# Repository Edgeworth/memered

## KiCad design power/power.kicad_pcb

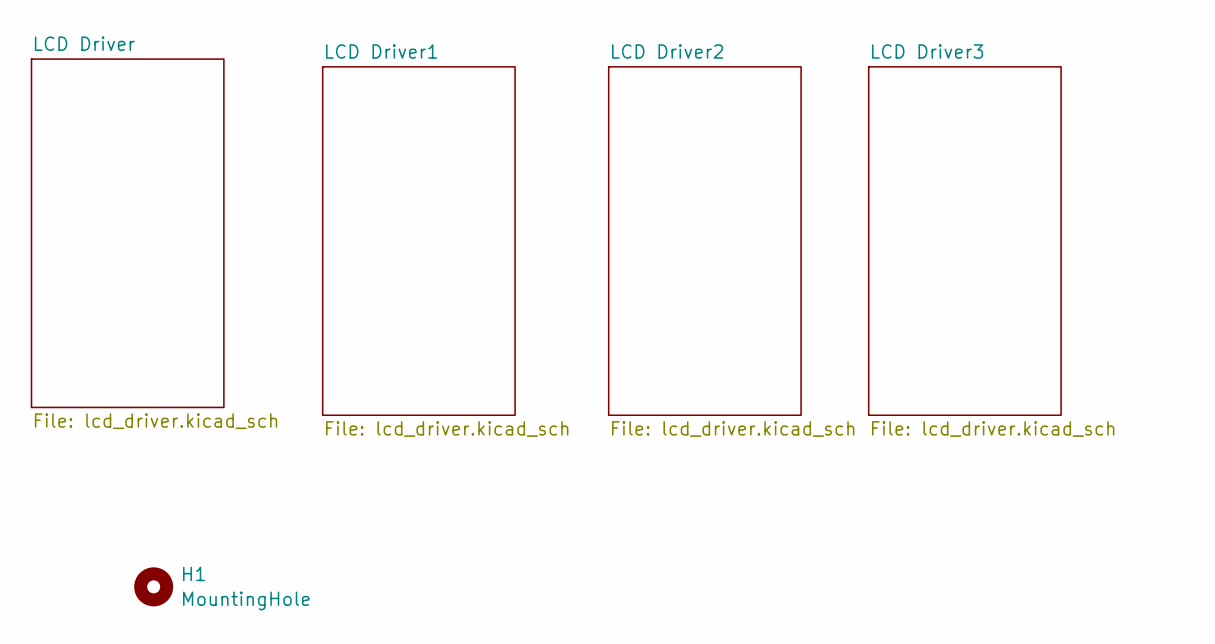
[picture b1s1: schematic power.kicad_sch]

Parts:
H1: MountingHole; MountingHole_2.2mm_M2

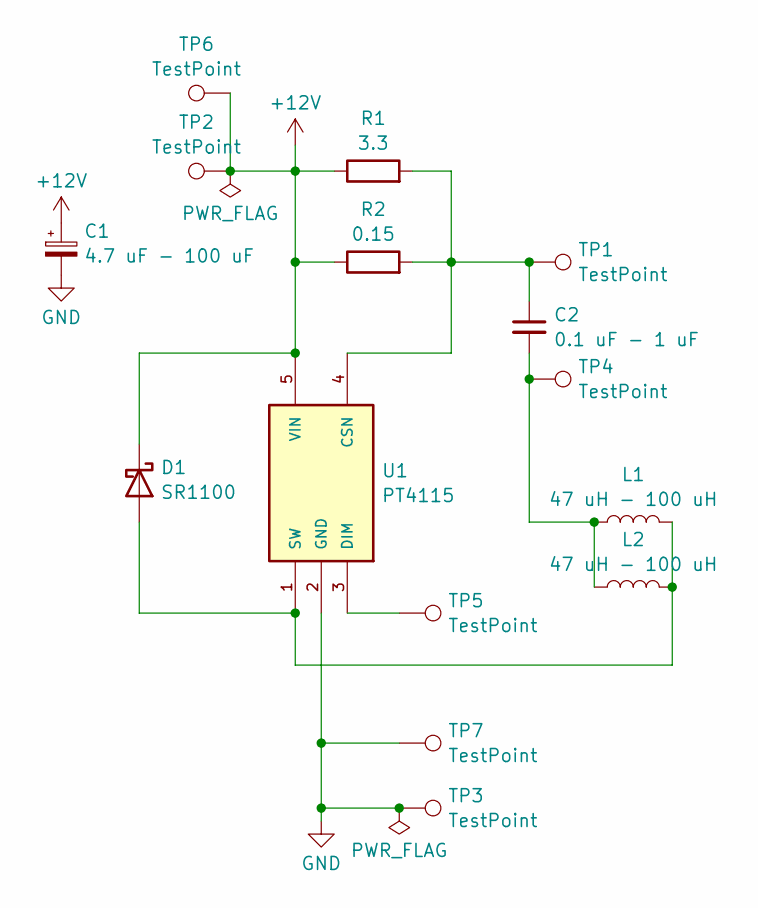
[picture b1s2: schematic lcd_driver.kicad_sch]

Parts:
C1: 4.7 uF - 100 uF; CP_Radial_D6.3mm_P2.50mm
C2: 0.1 uF - 1 uF; C_Disc_D6.0mm_W2.5mm_P5.00mm
D1: SR1100; D_DO-35_SOD27_P7.62mm_Horizontal
L1, L2: 47 uH - 100 uH; L_Axial_L9.5mm_D4.0mm_P12.70mm_Horizontal_Fastron_SMCC
R1: 3.3; R_Axial_DIN0207_L6.3mm_D2.5mm_P7.62mm_Horizontal
R2: 0.15; R_Axial_DIN0207_L6.3mm_D2.5mm_P7.62mm_Horizontal
TP1, TP2, TP3, TP4, TP5: TestPoint; TestPoint_THTPad_D1.5mm_Drill0.7mm
TP6, TP7: TestPoint; TestPoint_THTPad_D3.0mm_Drill1.5mm
U1: PT4115; SOT-89-5

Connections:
+12V: C1.1, D1.1 (K), R1.1, R2.1, TP2.1, TP6.1, U1.5 (VIN); also elsewhere on the board
GND: C1.2, TP3.1, TP7.1, U1.2 (GND); also elsewhere on the board
unnamed: C2.2, L1.1, L2.1, TP4.1
unnamed: D1.2 (A), L1.2, L2.2, U1.1 (SW)
unnamed: C2.1, R1.2, R2.2, TP1.1, U1.4 (CSN)
unnamed: TP5.1, U1.3 (DIM)

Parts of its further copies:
C3, C5, C7: 4.7 uF - 100 uF; CP_Radial_D6.3mm_P2.50mm
C4, C6, C8: 0.1 uF - 1 uF; C_Disc_D6.0mm_W2.5mm_P5.00mm
D2, D3, D4: SR1100; D_DO-35_SOD27_P7.62mm_Horizontal
L3, L4, L5, L6, L7, L8: 47 uH - 100 uH; L_Axial_L9.5mm_D4.0mm_P12.70mm_Horizontal_Fastron_SMCC
R3, R5, R7: 3.3; R_Axial_DIN0207_L6.3mm_D2.5mm_P7.62mm_Horizontal
R4, R6, R8: 0.15; R_Axial_DIN0207_L6.3mm_D2.5mm_P7.62mm_Horizontal
TP8, TP11, TP15, TP18, TP22, TP25: TestPoint; TestPoint_THTPad_D3.0mm_Drill1.5mm
TP9, TP10, TP12, TP13, TP14, TP16, TP17, TP19, TP20, TP21, TP23, TP24, TP26, TP27, TP28: TestPoint; TestPoint_THTPad_D1.5mm_Drill0.7mm
U2, U3, U4: PT4115; SOT-89-5

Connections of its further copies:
+12V: C3.1, C5.1, C7.1, D2.1 (K), D3.1 (K), D4.1 (K), R3.1, R4.1, R5.1, R6.1, R7.1, R8.1, TP8.1, TP9.1, TP15.1, TP16.1, TP22.1, TP23.1, U2.5 (VIN), U3.5 (VIN), U4.5 (VIN); also elsewhere on the board
GND: C3.2, C5.2, C7.2, TP11.1, TP12.1, TP18.1, TP19.1, TP25.1, TP26.1, U2.2 (GND), U3.2 (GND), U4.2 (GND); also elsewhere on the board
unnamed: C4.2, L3.1, L4.1, TP14.1
unnamed: C6.2, L5.1, L6.1, TP21.1
unnamed: C8.2, L7.1, L8.1, TP28.1
unnamed: D2.2 (A), L3.2, L4.2, U2.1 (SW)
unnamed: D3.2 (A), L5.2, L6.2, U3.1 (SW)
unnamed: D4.2 (A), L7.2, L8.2, U4.1 (SW)
unnamed: C4.1, R3.2, R4.2, TP13.1, U2.4 (CSN)
unnamed: TP10.1, U2.3 (DIM)
unnamed: C6.1, R5.2, R6.2, TP20.1, U3.4 (CSN)
unnamed: TP17.1, U3.3 (DIM)
unnamed: C8.1, R7.2, R8.2, TP27.1, U4.4 (CSN)
unnamed: TP24.1, U4.3 (DIM)

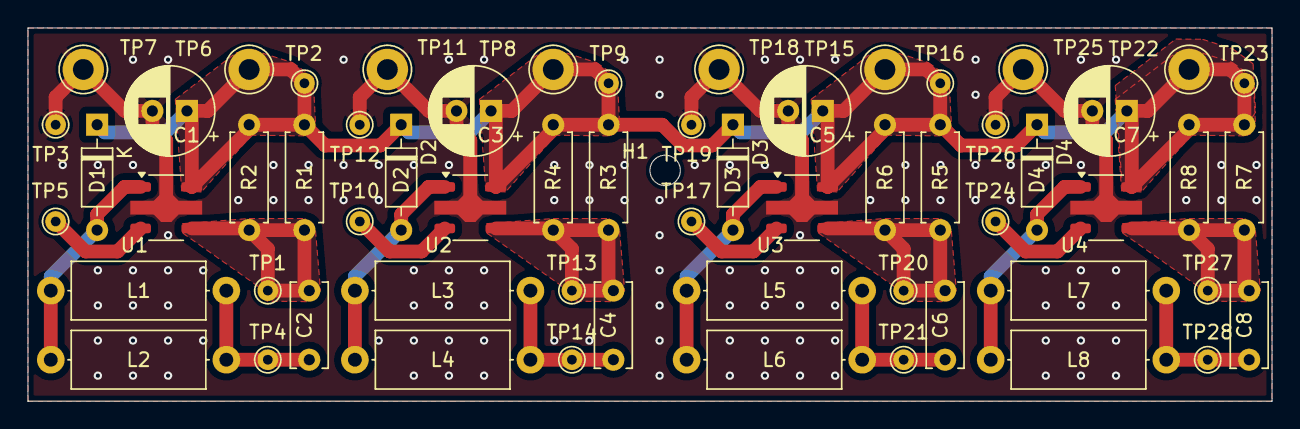
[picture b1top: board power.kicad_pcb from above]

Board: 2 copper layers, 90.0 x 27.0 mm, 61 parts (0 on the bottom side), 18 nets.

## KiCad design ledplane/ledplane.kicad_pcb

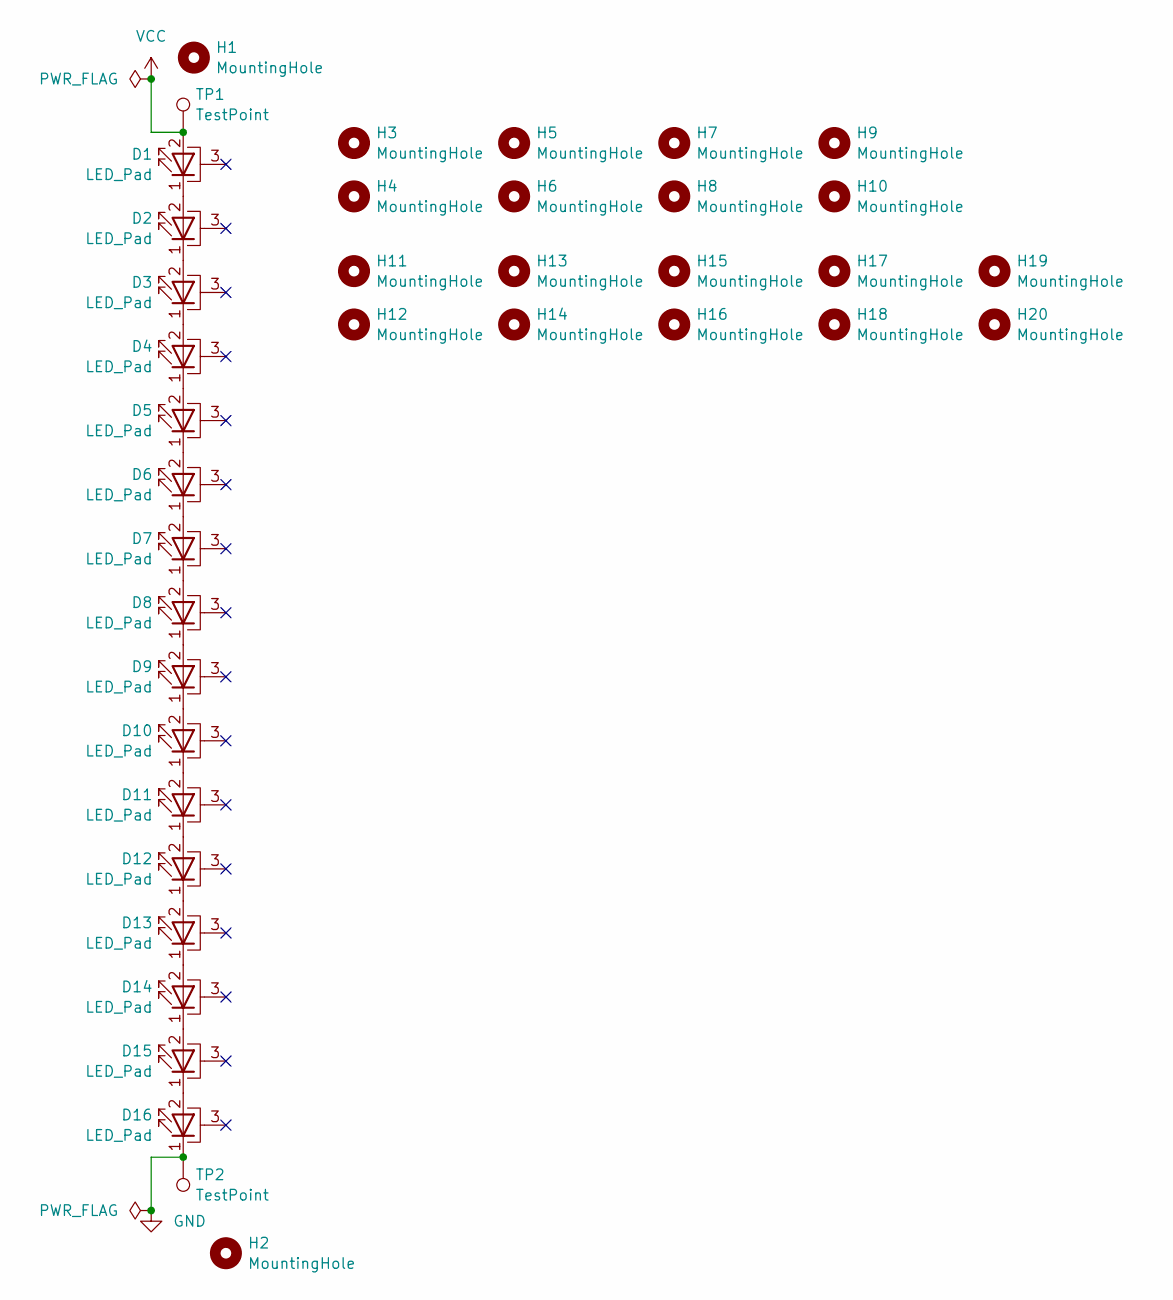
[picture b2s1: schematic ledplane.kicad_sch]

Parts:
D1, D2, D3, D4, D5, D6, D7, D8, D9, D10, D11, D12, D13, D14, D15, D16: LED_Pad; LED_3W_OTDIODE_COMBINED
H1, H2: MountingHole; MountingHole_2.2mm_M2
H3, H4, H5, H6, H7, H8, H9, H10, H11, H12, H13, H14, H15, H16, H17, H18, H19, H20: MountingHole; MountingHole_3.2mm_M3
TP1, TP2: TestPoint; SolderWirePad_1x01_SMD_4x6mm

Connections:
GND: D16.1 (K), TP2.1
unnamed: D1.1 (K), D2.2 (A)
unnamed: D2.1 (K), D3.2 (A)
unnamed: D3.1 (K), D4.2 (A)
unnamed: D4.1 (K), D5.2 (A)
unnamed: D5.1 (K), D6.2 (A)
unnamed: D6.1 (K), D7.2 (A)
unnamed: D7.1 (K), D8.2 (A)
unnamed: D8.1 (K), D9.2 (A)
unnamed: D9.1 (K), D10.2 (A)
unnamed: D10.1 (K), D11.2 (A)
unnamed: D11.1 (K), D12.2 (A)
unnamed: D12.1 (K), D13.2 (A)
unnamed: D13.1 (K), D14.2 (A)
unnamed: D14.1 (K), D15.2 (A)
unnamed: D15.1 (K), D16.2 (A)
VCC: D1.2 (A), TP1.1

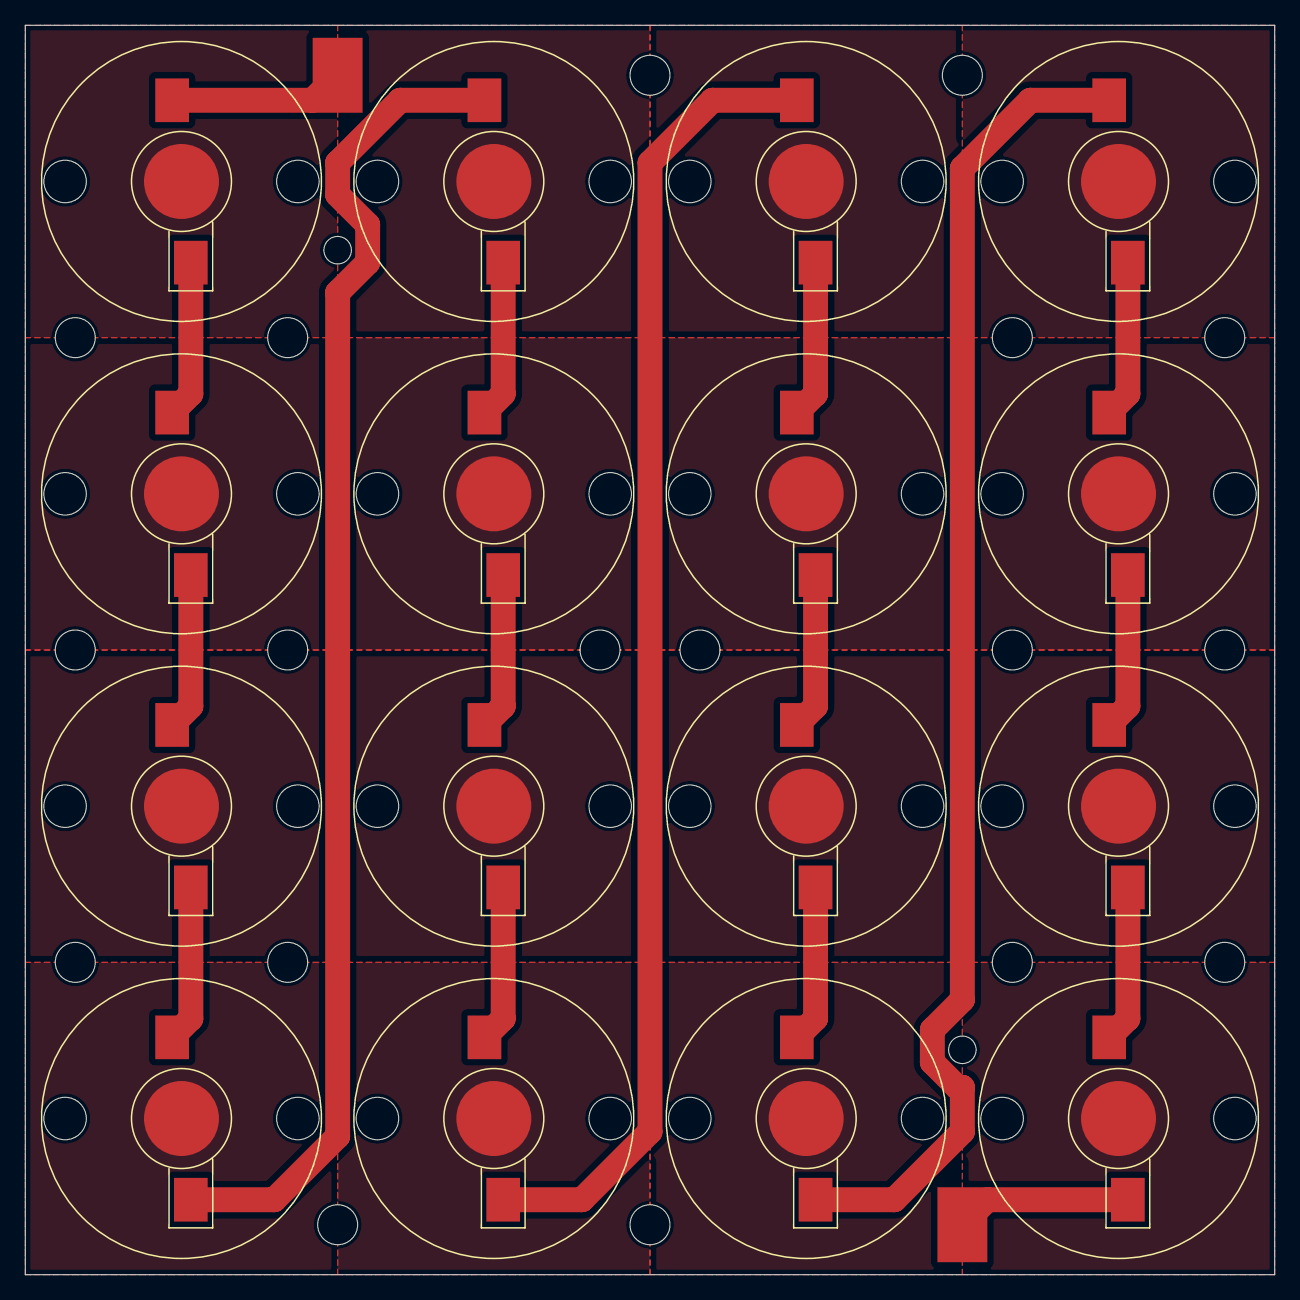
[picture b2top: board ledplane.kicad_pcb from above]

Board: 2 copper layers, 100.0 x 100.0 mm, 38 parts (0 on the bottom side), 17 nets.

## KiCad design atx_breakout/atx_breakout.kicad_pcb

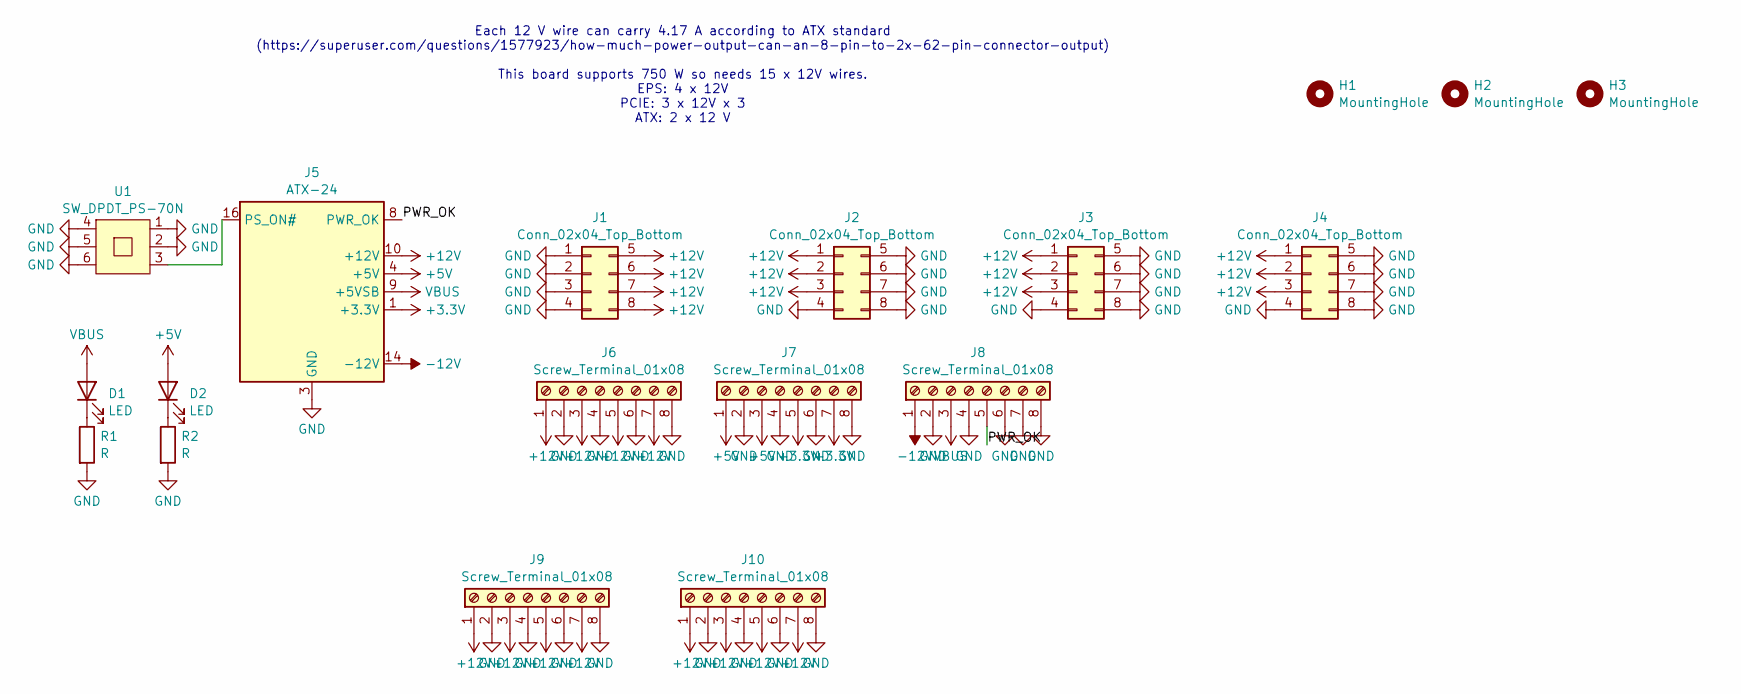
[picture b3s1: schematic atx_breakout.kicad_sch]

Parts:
D1, D2: LED; LED_D5.0mm
H1, H2, H3: MountingHole; MountingHole_2.2mm_M2
J1, J2, J3, J4: Conn_02x04_Top_Bottom; Molex_Mini-Fit_Jr_5566-08A_2x04_P4.20mm_XY_Vertical
J5: ATX-24; Molex_Mini-Fit_Jr_5566-24A_2x12_P4.20mm_XY_Vertical
J6, J7, J8: Screw_Terminal_01x08; TerminalBlock_Phoenix_PT-1,5-8-3.5-H_1x08_P3.50mm_Horizontal
J9, J10: Screw_Terminal_01x08; TerminalBlock_Phoenix_PT-1,5-8-5.0-H_1x08_P5.00mm_Horizontal
R1, R2: R; R_Axial_DIN0207_L6.3mm_D2.5mm_P7.62mm_Horizontal
U1: SW_DPDT_PS-70N

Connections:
+3.3V: J5.1 (+3.3V), J5.2 (+3.3V), J5.12 (+3.3V), J5.13 (+3.3V), J7.5, J7.7
+5V: D2.2 (A), J5.4 (+5V), J5.6 (+5V), J5.21 (+5V), J5.22 (+5V), J5.23 (+5V), J7.1, J7.3
+12V: J1.5, J1.6, J1.7, J1.8, J2.1, J2.2, J2.3, J3.1, J3.2, J3.3, J4.1, J4.2, J4.3, J5.10 (+12V), J5.11 (+12V), J6.1, J6.3, J6.5, J6.7, J9.1, J9.3, J9.5, J9.7, J10.1, J10.3, J10.5, J10.7
-12V: J5.14 (-12V), J8.1
/PWR_OK: J5.8 (PWR_OK), J8.5
GND: J1.1, J1.2, J1.3, J1.4, J2.4, J2.5, J2.6, J2.7, J2.8, J3.4, J3.5, J3.6, J3.7, J3.8, J4.4, J4.5, J4.6, J4.7, J4.8, J5.3 (GND), J5.5 (GND), J5.7 (GND), J5.15 (GND), J5.17 (GND), J5.18 (GND), J5.19 (GND), J5.24 (GND), J6.2, J6.4, J6.6, J6.8, J7.2, J7.4, J7.6, J7.8, J8.2, J8.4, J8.6, J8.7, J8.8, J9.2, J9.4, J9.6, J9.8, J10.2, J10.4, J10.6, J10.8, R1.2, R2.2, U1.1, U1.2, U1.4, U1.5, U1.6
unnamed: D1.1 (K), R1.1
unnamed: D2.1 (K), R2.1
unnamed: J5.16 (PS_ON#), U1.3
VBUS: D1.2 (A), J5.9 (+5VSB), J8.3

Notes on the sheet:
Each 12 V wire can carry 4.17 A according to ATX standard (https://superuser.com/questions/1577923/how-much-power-output-can-an-8-pin-to-2x-62-pin-connector-output) This board supports 750 W so needs 15 x 12V wires. EPS: 4 x 12V PCIE: 3 x 12V x 3 ATX: 2 x 12 V

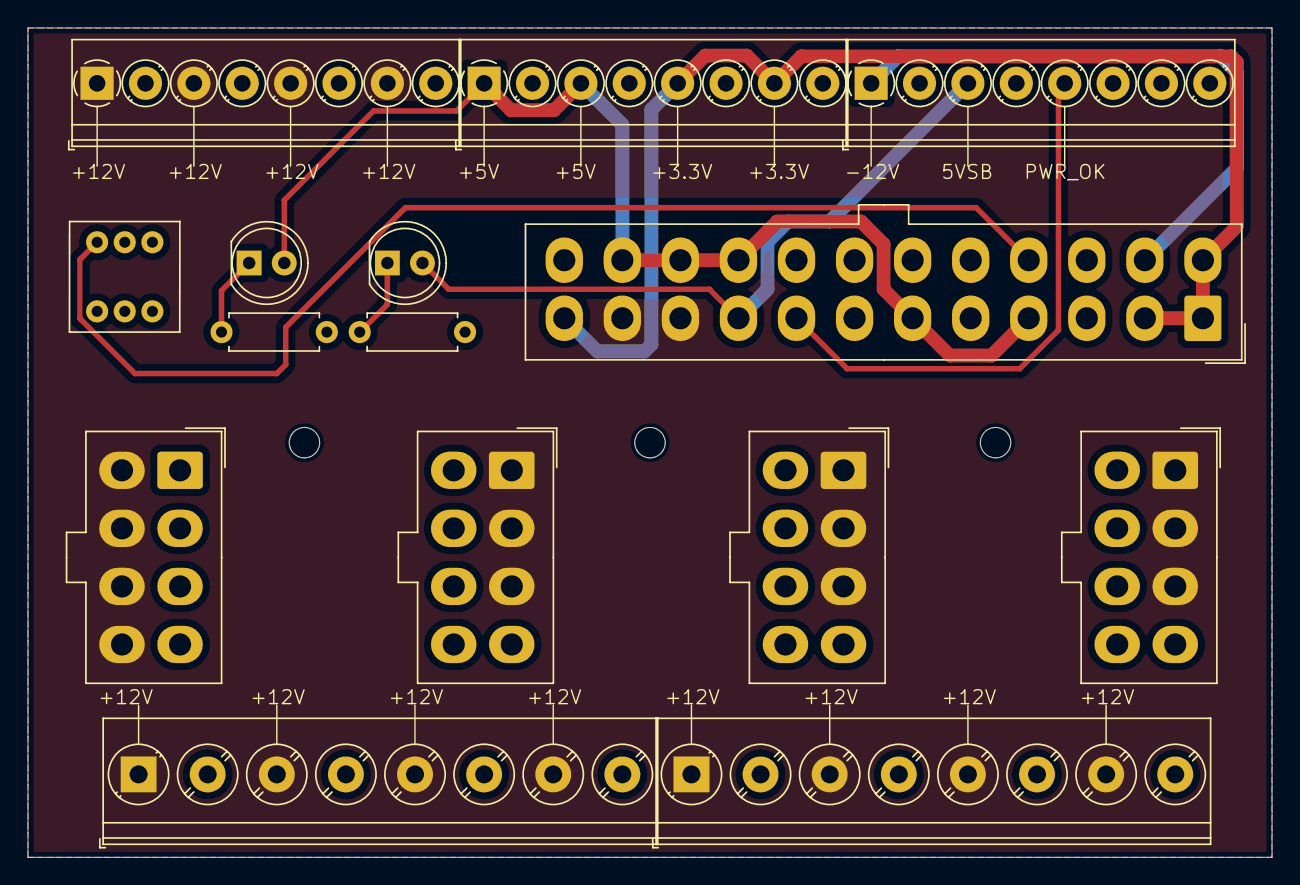
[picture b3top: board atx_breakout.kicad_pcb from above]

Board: 2 copper layers, 90.0 x 60.0 mm, 18 parts (0 on the bottom side), 10 nets.

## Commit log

2024-11-10 Progress
2024-11-21 Add radiometer cover
2024-12-01 Move around and update
2024-12-07 Add PCBs
2024-12-08 Backplane work
2024-12-08 Backplane done?
2024-12-08 Add gerbers
2024-12-08 Progress on atx breakout
2024-12-09 Finished atx breakout
2024-12-10 Add atx gerbers
2024-12-11 Add aluminium pcb for led plane
2024-12-13 Update ledplane
2024-12-22 Fix bugs (gerbers not updated)
2025-04-06 Update version
2025-04-06 Update LED plane to be all in series
2025-04-07 Rename
2025-05-18 Start modifying power board
